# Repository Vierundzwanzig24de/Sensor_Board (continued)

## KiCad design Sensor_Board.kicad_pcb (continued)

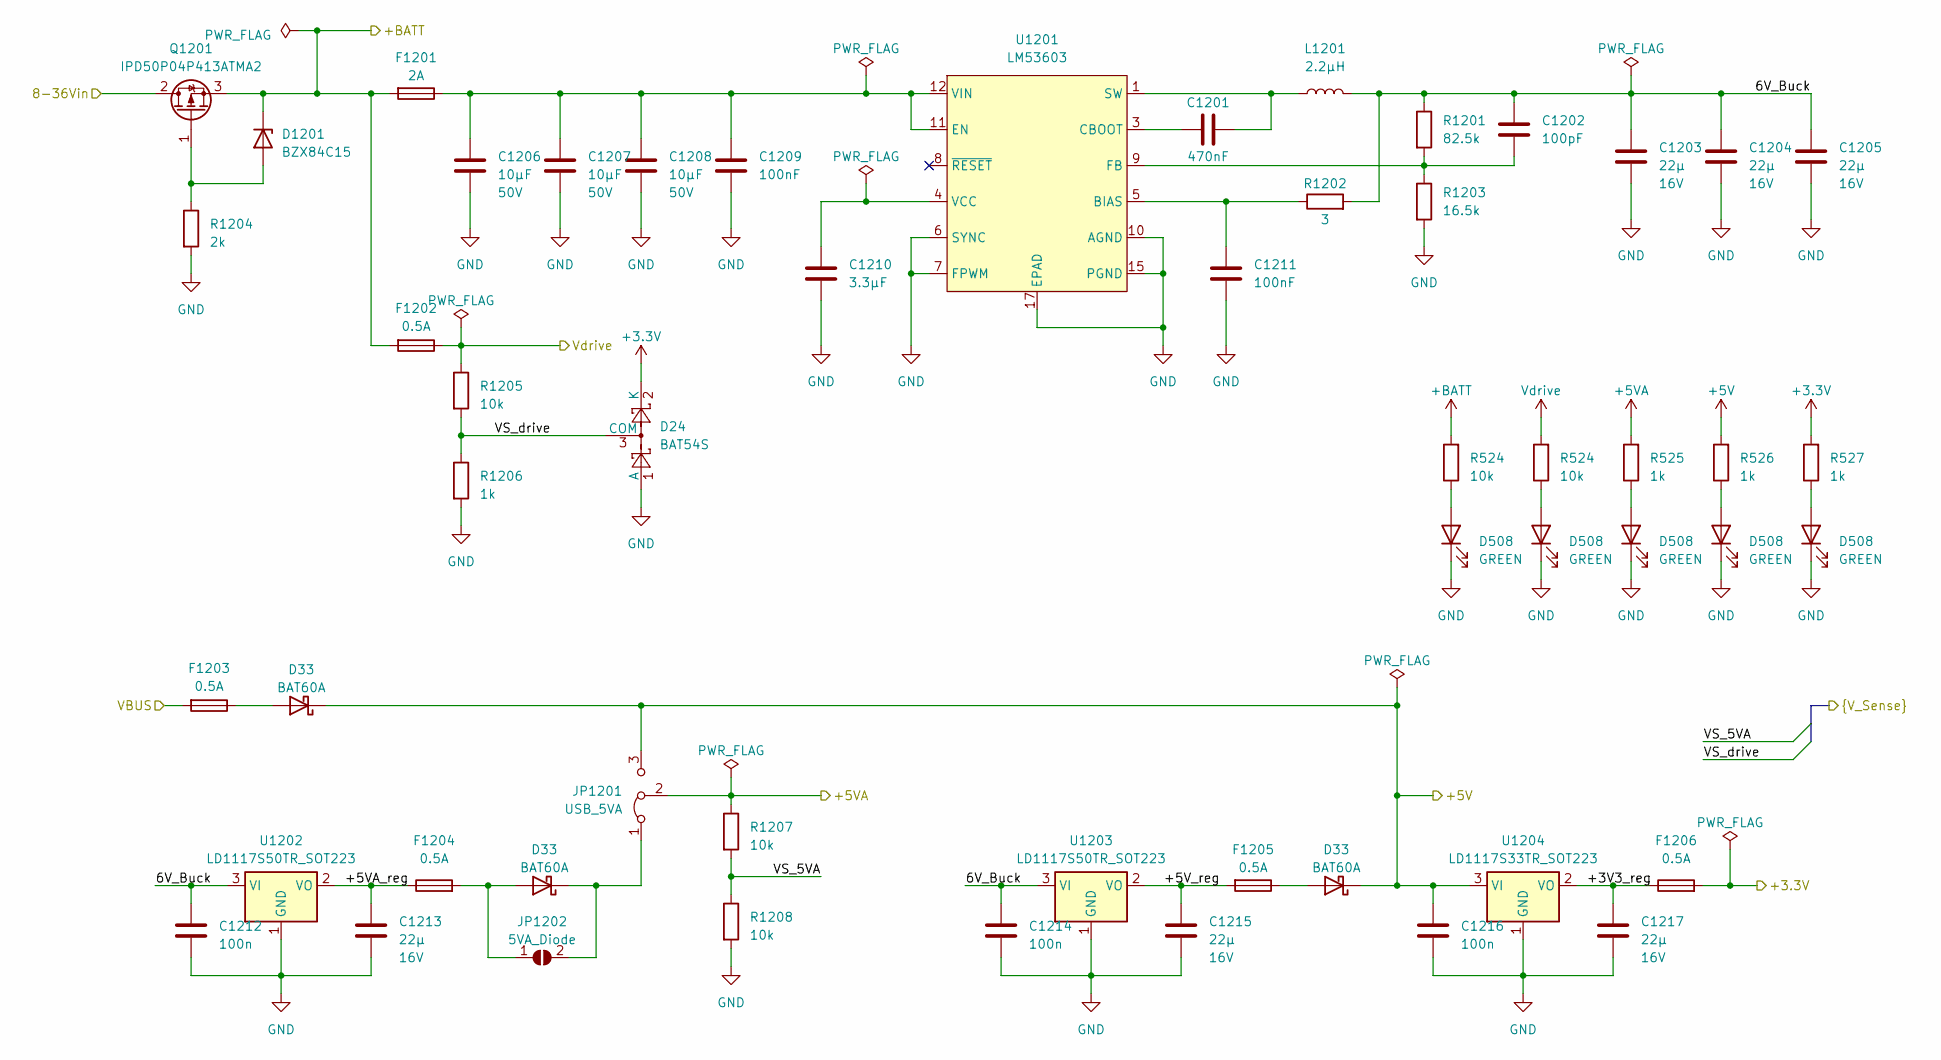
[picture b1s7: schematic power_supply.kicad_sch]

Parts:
C1201: 470nF; C_0805_2012Metric
C1202: 100pF; R_0603_1608Metric
C1203, C1204, C1205, C1213, C1215, C1217: 22µ; C_1210_3225Metric; Voltage 16V
C1206, C1207, C1208: 10µF; C_1206_3216Metric; Voltage 50V
C1209, C1211: 100nF; R_0603_1608Metric
C1210: 3.3µF; C_1206_3216Metric
C1212, C1214, C1216: 100n; C_0603_1608Metric
D24: BAT54S; SOT-23
D33: BAT60A; D_SOD-323
D508: GREEN; LED_0603_1608Metric
D1201: BZX84C15; SOT-23
F1201: 2A; Fuse_1206_3216Metric
F1202, F1203, F1204, F1205, F1206: 0.5A; Fuse_1206_3216Metric
JP1201: USB_5VA; PinHeader_1x03_P2.54mm_Vertical
JP1202: 5VA_Diode; SolderJumper-2_P1.3mm_Open_Pad1.0x1.5mm
L1201: 2.2µH; L_Bourns_SRP7028A_7.3x6.6mm
Q1201: IPD50P04P413ATMA2; TO-252-2
R524, R1205, R1207, R1208: 10k; R_0603_1608Metric
R525, R526, R527, R1206: 1k; R_0603_1608Metric
R1201: 82.5k; R_0603_1608Metric
R1202: 3; R_0603_1608Metric
R1203: 16.5k; R_0603_1608Metric
R1204: 2k; R_0603_1608Metric
U1201: LM53603; HTSSOP-16-1EP_4.4x5mm_P0.65mm_EP3.4x5mm_Mask2.46x2.31mm
U1202, U1203: LD1117S50TR_SOT223; SOT-223-3_TabPin2
U1204: LD1117S33TR_SOT223; SOT-223-3_TabPin2

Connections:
1A_Out1: R525.2; also elsewhere on the board
1A_Out2: R526.2; also elsewhere on the board
+5V: C1216.1, JP1201.3 (B), U1204.3 (VI); also elsewhere on the board
+5VA: JP1201.2 (C), R1207.1; also elsewhere on the board
+BATT: D1201.3 (K), F1201.2, F1202.2, Q1201.3 (S); also elsewhere on the board
/Connectors/VIN: Q1201.2 (D); also elsewhere on the board
/Microcontroller/VS_5VA: R1207.2, R1208.1; also elsewhere on the board
/Microcontroller/VS_drive: R1205.2, R1206.1; also elsewhere on the board
/Power Supply/6V_Buck: C1202.1, C1203.1, C1204.1, C1205.1, C1212.1, C1214.1, L1201.2, R1201.1, R1202.2, U1202.3 (VI), U1203.3 (VI)
/Power Supply/+3V3_reg: C1217.1, F1206.1, U1204.2 (VO)
/Power Supply/+5VA_reg: C1213.1, F1204.1, U1202.2 (VO)
/Power Supply/+5V_reg: C1215.1, F1205.2, U1203.2 (VO)
/Power Supply/VBUS: F1203.2; also elsewhere on the board
unnamed: C1201.2, L1201.1, U1201.1 (SW), U1201.2 (SW)
unnamed: D1201.1 (A), Q1201.1 (G), R1204.1
unnamed 151: F1203.1; also elsewhere on the board
unnamed 152: F1204.2, JP1202.1 (A); also elsewhere on the board
unnamed 153: JP1201.1 (A), JP1202.2 (B); also elsewhere on the board
unnamed 154: F1205.1; also elsewhere on the board
unnamed: C1211.1, R1202.1, U1201.5 (BIAS)
unnamed: C1201.1, U1201.3 (CBOOT)
unnamed: C1202.2, R1201.2, R1203.1, U1201.9 (FB)
unnamed: C1210.1, U1201.4 (VCC)
VIN: C1206.1, C1207.1, C1208.1, C1209.1, F1201.1, U1201.11 (EN), U1201.12 (VIN), U1201.13 (VIN)

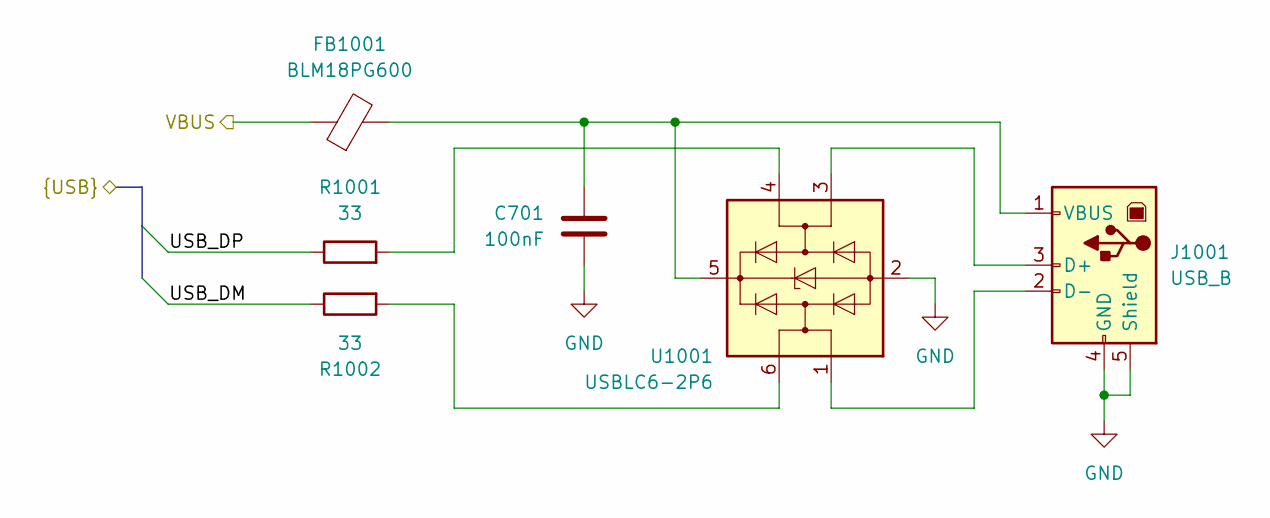
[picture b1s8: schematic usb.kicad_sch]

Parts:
C701: 100nF; C_0603_1608Metric
FB1001: BLM18PG600; L_0603_1608Metric
J1001: USB_B; USB_B_OST_USB-B1HSxx_Horizontal
R1001, R1002: 33; R_0603_1608Metric
U1001: USBLC6-2P6; SOT-666

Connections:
/Microcontroller/USB_DM: R1002.1; also elsewhere on the board
/Microcontroller/USB_DP: R1001.1; also elsewhere on the board
/Power Supply/VBUS: FB1001.1; also elsewhere on the board
unnamed: J1001.3 (D+), U1001.3 (I/O2)
unnamed: J1001.2 (D-), U1001.1 (I/O1)
unnamed: R1001.2, U1001.4 (I/O2)
unnamed: R1002.2, U1001.6 (I/O1)

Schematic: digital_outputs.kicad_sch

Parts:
D601, D602, D603, D604, D605, D606, D607, D608: BAT54S; SOT-23
JP601: DOut_Supply0; PinHeader_1x03_P2.54mm_Vertical
JP602: DOut_Supply1; PinHeader_1x03_P2.54mm_Vertical
Q601, Q602, Q603, Q604, Q605, Q606, Q607, Q608, Q613, Q614, Q615, Q616, Q617, Q618, Q619, Q620: BC817; SOT-23
Q609, Q610, Q611, Q612, Q621, Q622, Q623, Q624: BC807; SOT-23
R601, R603, R605, R607, R625, R627, R629, R631: 10k; R_0603_1608Metric
R602, R604, R606, R608, R609, R610, R611, R612, R613, R614, R615, R616, R617, R618, R619, R620, R621, R622, R623, R624, R626, R628, R630, R632, R633, R634, R635, R636, R637, R638, R639, R640, R641, R642, R643, R644, R645, R646, R647, R648: 1k; R_0603_1608Metric

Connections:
+5V: JP601.3 (B), JP602.3 (B); also elsewhere on the board
/Digital Outputs/DOut_Supply0: JP601.2 (C), Q601.3 (C), Q602.3 (C), Q603.3 (C), Q604.3 (C), R601.1, R603.1, R605.1, R607.1
/Digital Outputs/DOut_Supply1: JP602.2 (C), Q613.3 (C), Q614.3 (C), Q615.3 (C), Q616.3 (C), R625.1, R627.1, R629.1, R631.1
/Digital Outputs/D_Out_3V3_0: R617.1; also elsewhere on the board
/Digital Outputs/D_Out_3V3_1: R619.1; also elsewhere on the board
/Digital Outputs/D_Out_3V3_2: R621.1; also elsewhere on the board
/Digital Outputs/D_Out_3V3_3: R623.1; also elsewhere on the board
/Digital Outputs/D_Out_3V3_4: R641.1; also elsewhere on the board
/Digital Outputs/D_Out_3V3_5: R643.1; also elsewhere on the board
/Digital Outputs/D_Out_3V3_6: R645.1; also elsewhere on the board
/Digital Outputs/D_Out_3V3_7: R647.1; also elsewhere on the board
D_Out_0: D601.3; also elsewhere on the board
D_Out_1: D602.3; also elsewhere on the board
D_Out_2: D603.3; also elsewhere on the board
D_Out_3: D604.3; also elsewhere on the board
D_Out_4: D605.3; also elsewhere on the board
D_Out_5: D606.3; also elsewhere on the board
D_Out_6: D607.3; also elsewhere on the board
D_Out_7: D608.3; also elsewhere on the board
unnamed: D601.1, R609.2
unnamed: D601.2, R613.1
unnamed: D602.1, R610.2
unnamed: D602.2, R614.1
unnamed: D603.1, R611.2
unnamed: D603.2, R615.1
unnamed: D604.1, R612.2
unnamed: D604.2, R616.1
unnamed: D605.1, R633.2
unnamed: D605.2, R637.1
unnamed: D606.1, R634.2
unnamed: D606.2, R638.1
unnamed: D607.1, R635.2
unnamed: D607.2, R639.1
unnamed: D608.1, R636.2
unnamed: D608.2, R640.1
unnamed: Q601.1 (B), R602.1
unnamed: Q601.2 (E), R609.1
unnamed: Q602.1 (B), R604.1
unnamed: Q602.2 (E), R610.1
unnamed: Q603.1 (B), R606.1
unnamed: Q603.2 (E), R611.1
unnamed: Q604.1 (B), R608.1
unnamed: Q604.2 (E), R612.1
unnamed: Q605.1 (B), R617.2
unnamed: Q605.3 (C), R601.2, R602.2, R618.1
unnamed: Q606.1 (B), R619.2
unnamed: Q606.3 (C), R603.2, R604.2, R620.1
unnamed: Q607.1 (B), R621.2
unnamed: Q607.3 (C), R605.2, R606.2, R622.1
unnamed: Q608.1 (B), R623.2
unnamed: Q608.3 (C), R607.2, R608.2, R624.1
unnamed: Q609.1 (B), R618.2
unnamed: Q609.2 (E), R613.2
unnamed: Q610.1 (B), R620.2
unnamed: Q610.2 (E), R614.2
unnamed: Q611.1 (B), R622.2
unnamed: Q611.2 (E), R615.2
unnamed: Q612.1 (B), R624.2
unnamed: Q612.2 (E), R616.2
unnamed: Q613.1 (B), R626.1
unnamed: Q613.2 (E), R633.1
unnamed: Q614.1 (B), R628.1
unnamed: Q614.2 (E), R634.1
unnamed: Q615.1 (B), R630.1
unnamed: Q615.2 (E), R635.1
unnamed: Q616.1 (B), R632.1
unnamed: Q616.2 (E), R636.1
unnamed: Q617.1 (B), R641.2
unnamed: Q617.3 (C), R625.2, R626.2, R642.1
unnamed: Q618.1 (B), R643.2
unnamed: Q618.3 (C), R627.2, R628.2, R644.1
unnamed: Q619.1 (B), R645.2
unnamed: Q619.3 (C), R629.2, R630.2, R646.1
unnamed: Q620.1 (B), R647.2
unnamed: Q620.3 (C), R631.2, R632.2, R648.1
unnamed: Q621.1 (B), R642.2
unnamed: Q621.2 (E), R637.2
unnamed: Q622.1 (B), R644.2
unnamed: Q622.2 (E), R638.2
unnamed: Q623.1 (B), R646.2
unnamed: Q623.2 (E), R639.2
unnamed: Q624.1 (B), R648.2
unnamed: Q624.2 (E), R640.2

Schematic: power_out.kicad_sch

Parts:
C501, C507: 220µ; CP_Elec_10x10.5
C502, C504: 1n; C_0603_1608Metric
C503, C505, C508, C509, C510, C511, C512, C513, C518: 100nF; C_0603_1608Metric
C506: 100p; C_0603_1608Metric
C514, C515, C516, C517: 10n; C_0603_1608Metric
C519: 1µ; C_0603_1608Metric
D501, D502, D503, D504, D513: PMEG4010CEH; D_SOD-123F
D506, D507, D508, D509, D510, D511: BLUE; LED_0603_1608Metric
D512: RED; LED_0603_1608Metric
Q501, Q502: BTN8962TA; TO-263-7_TabPin8
R501, R502, R505, R506, R514, R515, R516, R517, R518, R519, R520, R522, R523, R524, R525, R526, R527: 10k; R_0603_1608Metric
R503, R507, R528: 1k; R_0603_1608Metric
R504, R508: t.b.d.; R_0603_1608Metric
R509: 1.2k; R_0603_1608Metric
R510, R511, R512, R513: 100k; R_0603_1608Metric
R521: 27; R_0603_1608Metric
U501: BTT6200-4ESA; Infineon_PG-TSDSO-24

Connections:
1A_Out1: C516.1, D504.1 (K), R512.2, R525.2, U501.20 (OUT1); also elsewhere on the board
1A_Out2: C515.1, D503.1 (K), R511.2, R526.2, U501.17 (OUT2); also elsewhere on the board
+BATT: C501.1, C507.1, C509.1, C510.1, C511.1, C513.1, C518.1, C519.1, Q501.7, Q502.7, U501.25 (VS); also elsewhere on the board
/Microcontroller/1A_DSEL0: R514.1; also elsewhere on the board
/Microcontroller/1A_DSEL1: R515.1; also elsewhere on the board
/Microcontroller/1A_IN0: R516.1; also elsewhere on the board
/Microcontroller/1A_IN1: R517.1; also elsewhere on the board
/Microcontroller/1A_IN2: R518.1; also elsewhere on the board
/Microcontroller/1A_IN3: R519.1; also elsewhere on the board
/Microcontroller/1A_IS: C506.1, R520.2; also elsewhere on the board
/Microcontroller/Half0_IS: C502.1, Q501.6 (IS), R503.2; also elsewhere on the board
/Microcontroller/Half0_PWM: R502.1; also elsewhere on the board
/Microcontroller/Half1_IS: C504.1, Q502.6 (IS), R507.2; also elsewhere on the board
/Microcontroller/Half1_PWM: R506.1; also elsewhere on the board
/Microcontroller/Half_INH: D512.1 (K), R501.1, R505.1; also elsewhere on the board
Half0_OUT: C508.1, C509.2, Q501.4, Q501.8, R523.2; also elsewhere on the board
Half1_OUT: C511.2, C512.1, Q502.4, Q502.8, R522.2; also elsewhere on the board
unnamed: D501.2 (A), R521.1
unnamed: D506.2 (A), R523.1
unnamed: D507.2 (A), R522.1
unnamed: D512.2 (A), R528.1
unnamed: Q501.2 (IN), R502.2
unnamed: Q501.3 (INH), R501.2
unnamed: C503.1, Q501.5 (SR), R504.2
unnamed: Q502.2 (IN), R506.2
unnamed: Q502.3 (INH), R505.2
unnamed: C505.1, Q502.5 (SR), R508.2
unnamed: R514.2, U501.8 (DSEL0)
unnamed: R515.2, U501.11 (DSEL1)
unnamed: R521.2, U501.4 (GND)
unnamed: R516.2, U501.2 (IN0)
unnamed: R517.2, U501.5 (IN1)
unnamed: R518.2, U501.9 (IN2)
unnamed: R519.2, U501.10 (IN3)
unnamed: R509.2, R520.1, U501.7 (IS)

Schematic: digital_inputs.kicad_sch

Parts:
C301, C302, C303, C304, C305, C306, C309, C310: 100pF; C_0603_1608Metric
C307, C308: 100nF; C_0603_1608Metric
D301, D302, D303, D304, D305, D306, D307, D308, D309, D310, D311, D312, D313, D314, D315, D316: BAT54S; SOT-23
R301, R302, R303, R304, R305, R306, R307, R308: 100k; R_0603_1608Metric
RN301: 10k; R_Array_Convex_8x0602
U301: 74HC595; SOIC-16_3.9x9.9mm_P1.27mm
U302: 74HCT244; SOIC-20W_7.5x12.8mm_P1.27mm

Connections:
/ADC/IN_RCLK: U301.12 (RCLK); also elsewhere on the board
/ADC/IN_SRCLK: U301.11 (SRCLK); also elsewhere on the board
/ADC/IN_SRD: U301.14 (SER); also elsewhere on the board
/ADC/IN_SRD_AIn: U301.9 (QH'); also elsewhere on the board
/Connectors/D_In_0: D301.2 (K), R301.1; also elsewhere on the board
/Connectors/D_In_1: D302.2 (K), R302.1; also elsewhere on the board
/Connectors/D_In_2: D303.2 (K), R303.1; also elsewhere on the board
/Connectors/D_In_3: D307.2 (K), R304.1; also elsewhere on the board
/Connectors/D_In_4: D308.2 (K), R305.1; also elsewhere on the board
/Connectors/D_In_5: D309.2 (K), R306.1; also elsewhere on the board
/Connectors/D_In_6: D313.2 (K), R307.1; also elsewhere on the board
/Connectors/D_In_7: D314.2 (K), R308.1; also elsewhere on the board
/Digital Inputs/D_In_0_filt: C301.1, D304.3 (COM), R301.2, U302.2 (1A0)
/Digital Inputs/D_In_0_pullup: D301.1 (A), D301.3 (COM), RN301.16 (R1.2)
/Digital Inputs/D_In_1_filt: C302.1, D305.3 (COM), R302.2, U302.4 (1A1)
/Digital Inputs/D_In_1_pullup: D302.1 (A), D302.3 (COM), RN301.15 (R2.2)
/Digital Inputs/D_In_2_filt: C303.1, D306.3 (COM), R303.2, U302.6 (1A2)
/Digital Inputs/D_In_2_pullup: D303.1 (A), D303.3 (COM), RN301.14 (R3.2)
/Digital Inputs/D_In_3V3_0: U302.18 (1Y0); also elsewhere on the board
/Digital Inputs/D_In_3V3_1: U302.16 (1Y1); also elsewhere on the board
/Digital Inputs/D_In_3V3_2: U302.14 (1Y2); also elsewhere on the board
/Digital Inputs/D_In_3V3_3: U302.12 (1Y3); also elsewhere on the board
/Digital Inputs/D_In_3V3_4: U302.3 (2Y0); also elsewhere on the board
/Digital Inputs/D_In_3V3_5: U302.5 (2Y1); also elsewhere on the board
/Digital Inputs/D_In_3V3_6: U302.7 (2Y2); also elsewhere on the board
/Digital Inputs/D_In_3V3_7: U302.9 (2Y3); also elsewhere on the board
/Digital Inputs/D_In_3_filt: C304.1, D310.3 (COM), R304.2, U302.8 (1A3)
/Digital Inputs/D_In_3_pullup: D307.1 (A), D307.3 (COM), RN301.13 (R4.2)
/Digital Inputs/D_In_4_filt: C305.1, D311.3 (COM), R305.2, U302.17 (2A0)
/Digital Inputs/D_In_4_pullup: D308.1 (A), D308.3 (COM), RN301.12 (R5.2)
/Digital Inputs/D_In_5_filt: C306.1, D312.3 (COM), R306.2, U302.15 (2A1)
/Digital Inputs/D_In_5_pullup: D309.1 (A), D309.3 (COM), RN301.11 (R6.2)
/Digital Inputs/D_In_6_filt: C309.1, D315.3 (COM), R307.2, U302.13 (2A2)
/Digital Inputs/D_In_6_pullup: D313.1 (A), D313.3 (COM), RN301.10 (R7.2)
/Digital Inputs/D_In_7_filt: C310.1, D316.3 (COM), R308.2, U302.11 (2A3)
/Digital Inputs/D_In_7_pullup: D314.1 (A), D314.3 (COM), RN301.9 (R8.2)
unnamed: RN301.1 (R1.1), U301.15 (QA)
unnamed: RN301.2 (R2.1), U301.1 (QB)
unnamed: RN301.3 (R3.1), U301.2 (QC)
unnamed: RN301.4 (R4.1), U301.3 (QD)
unnamed: RN301.5 (R5.1), U301.4 (QE)
unnamed: RN301.6 (R6.1), U301.5 (QF)
unnamed: RN301.7 (R7.1), U301.6 (QG)
unnamed: RN301.8 (R8.1), U301.7 (QH)

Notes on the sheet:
1/(2*pi*100k*100pF) = 15.9kHz
Configurable Pull-up resistors If Qn is pulled to GND the in-series diode blocks reverse voltages and the input becomes "High-Z"

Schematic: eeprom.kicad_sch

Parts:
C701: 100nF; C_0603_1608Metric
JP701: SolderJumper_2_Open; SolderJumper-2_P1.3mm_Open_Pad1.0x1.5mm
R701, R702: 10k; R_0603_1608Metric
U701: 24LC32; SOIC-8_3.9x4.9mm_P1.27mm

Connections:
/EEPROM/EEPROM_SCL: R702.2, U701.6 (SCL); also elsewhere on the board
/EEPROM/EEPROM_SDA: R701.2, U701.5 (SDA); also elsewhere on the board
/EEPROM/EEPROM_WP: JP701.2 (B), U701.7 (WP); also elsewhere on the board

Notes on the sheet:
Pin A2 wired to Vcc to allow replacement with 24LC1025

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
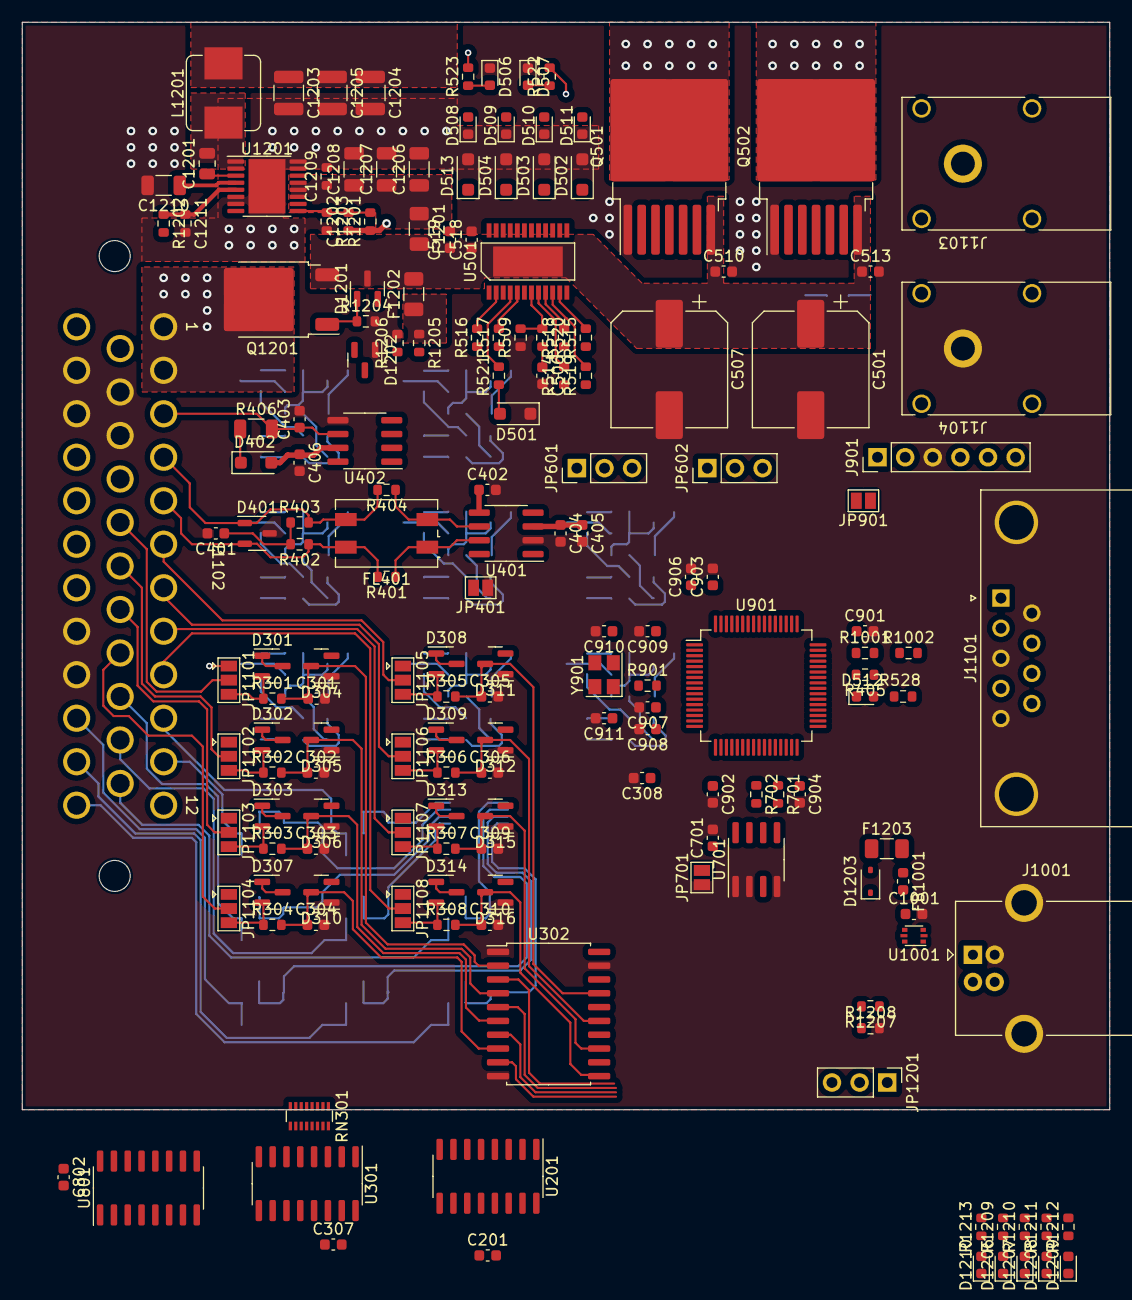
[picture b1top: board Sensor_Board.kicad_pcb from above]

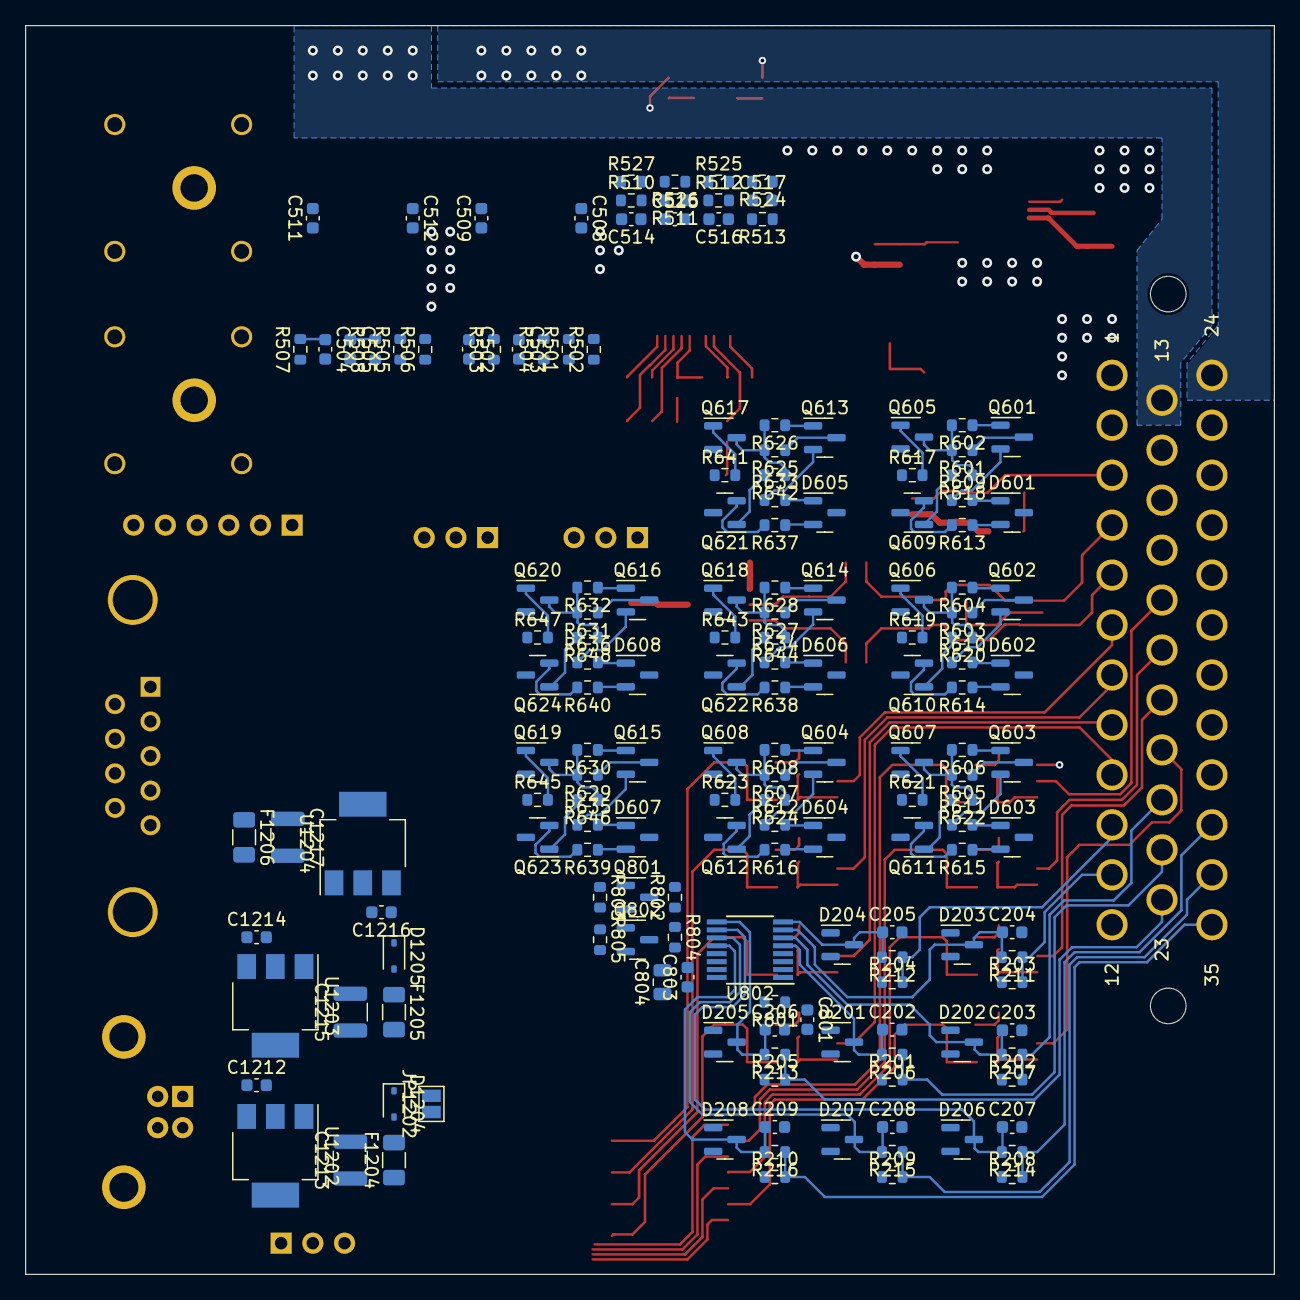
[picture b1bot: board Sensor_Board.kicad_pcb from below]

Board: 4 copper layers, 100.0 x 100.0 mm, 338 parts (166 on the bottom side), 266 nets.

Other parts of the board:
C901, C902, C903, C904, C909, C910, C911, C1001: 100nF; C_0603_1608Metric
C906: 4.7µ; C_0603_1608Metric
C907: 10n; C_0603_1608Metric
C908: 1µ; C_0603_1608Metric
D402: PMEG4010CEH; D_SOD-123F
D1202: BAT54S; SOT-23
D1203, D1204, D1205: BAT60A; D_SOD-323
D1206, D1207, D1208, D1209, D1210: GREEN; LED_0603_1608Metric
R801: 2k; R_0603_1608Metric
R1209, R1213: 10k; R_0603_1608Metric
R1210, R1211, R1212: 1k; R_0603_1608Metric

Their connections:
+5V: D1203.1 (K), D1205.1 (K), R1211.2; also elsewhere on the board
+5VA: R801.1, R1210.2; also elsewhere on the board
+BATT: R1213.2; also elsewhere on the board
/Microcontroller/VS_drive: D1202.3 (COM); also elsewhere on the board
unnamed 151: D1203.2 (A); also elsewhere on the board
unnamed 152: D1204.2 (A); also elsewhere on the board
unnamed 153: D1204.1 (K); also elsewhere on the board
unnamed 154: D1205.2 (A); also elsewhere on the board
unnamed: D1206.2 (A), R1209.1
unnamed: D1207.2 (A), R1210.1
unnamed: D1208.2 (A), R1211.1
unnamed: D1209.2 (A), R1212.1
unnamed: D1210.2 (A), R1213.1
unnamed 245: R801.2; also elsewhere on the board

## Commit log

2023-12-16 added gitignore
2023-12-16 cleaned up repository
2023-12-16 learned how to use gitignore
2023-12-16 now finally
2023-12-16 finally got gitignore working
2023-12-16 added net-classes
2023-12-17 completed schematic
2023-12-18 placed components and began routing
2023-12-20 majority of layout done
2023-12-20 finished layout
2023-12-20 added README
2023-12-20 generated BOM
2023-12-20 added ToDos
2023-12-23 fixed oscillator and component values
2023-12-26 hierarchical sheets for digital I/O and replaced power supply jumpers with relays
2024-01-02 Added LICENSE.txt
2024-01-04 added missing values and possible improvements
